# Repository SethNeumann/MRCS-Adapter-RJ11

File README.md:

# MRCS-Adapter-RJ11
## License: Creative Commons Attribution-NonCommercial-ShareAlike

MRCS - RJ modular Headset connector breakout board

RJ11/4 "mini" headset connector to 0.100 pins, for telephony applications

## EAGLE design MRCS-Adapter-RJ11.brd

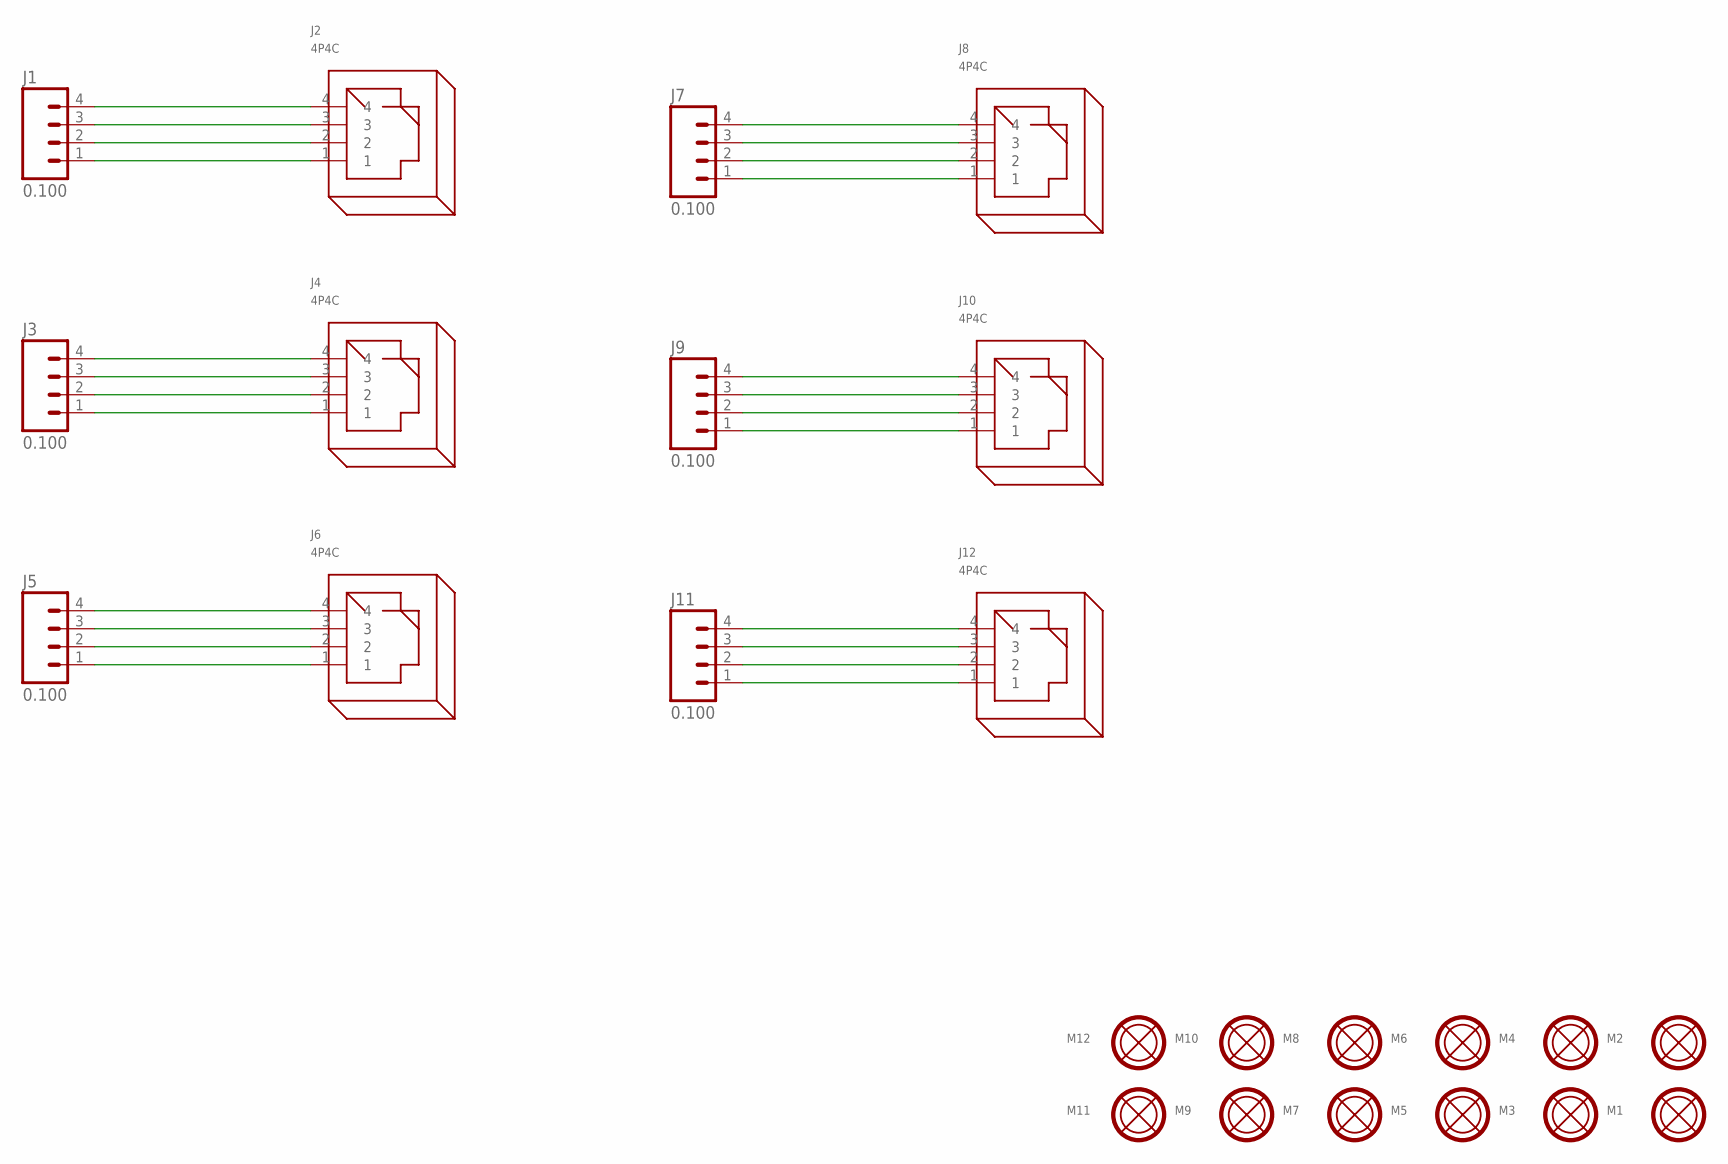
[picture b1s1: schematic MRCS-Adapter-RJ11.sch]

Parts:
J1, J3, J5, J7, J9, J11: 0.100; 1X04_LOCK
J2, J4, J6, J8, J10, J12: 4P4C; RJ11
M1, M2, M3, M4, M5, M6, M7, M8, M9, M10, M11, M12: MOUNTINGHOLE

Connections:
unnamed: J1.1, J2.1
unnamed: J1.2, J2.2
unnamed: J1.3, J2.3
unnamed: J1.4, J2.4
unnamed: J3.1, J4.1
unnamed: J3.2, J4.2
unnamed: J3.3, J4.3
unnamed: J3.4, J4.4
unnamed: J5.1, J6.1
unnamed: J5.2, J6.2
unnamed: J5.3, J6.3
unnamed: J5.4, J6.4
unnamed: J7.1, J8.1
unnamed: J7.2, J8.2
unnamed: J7.3, J8.3
unnamed: J7.4, J8.4
unnamed: J9.1, J10.1
unnamed: J9.2, J10.2
unnamed: J9.3, J10.3
unnamed: J9.4, J10.4
unnamed: J11.1, J12.1
unnamed: J11.2, J12.2
unnamed: J11.3, J12.3
unnamed: J11.4, J12.4

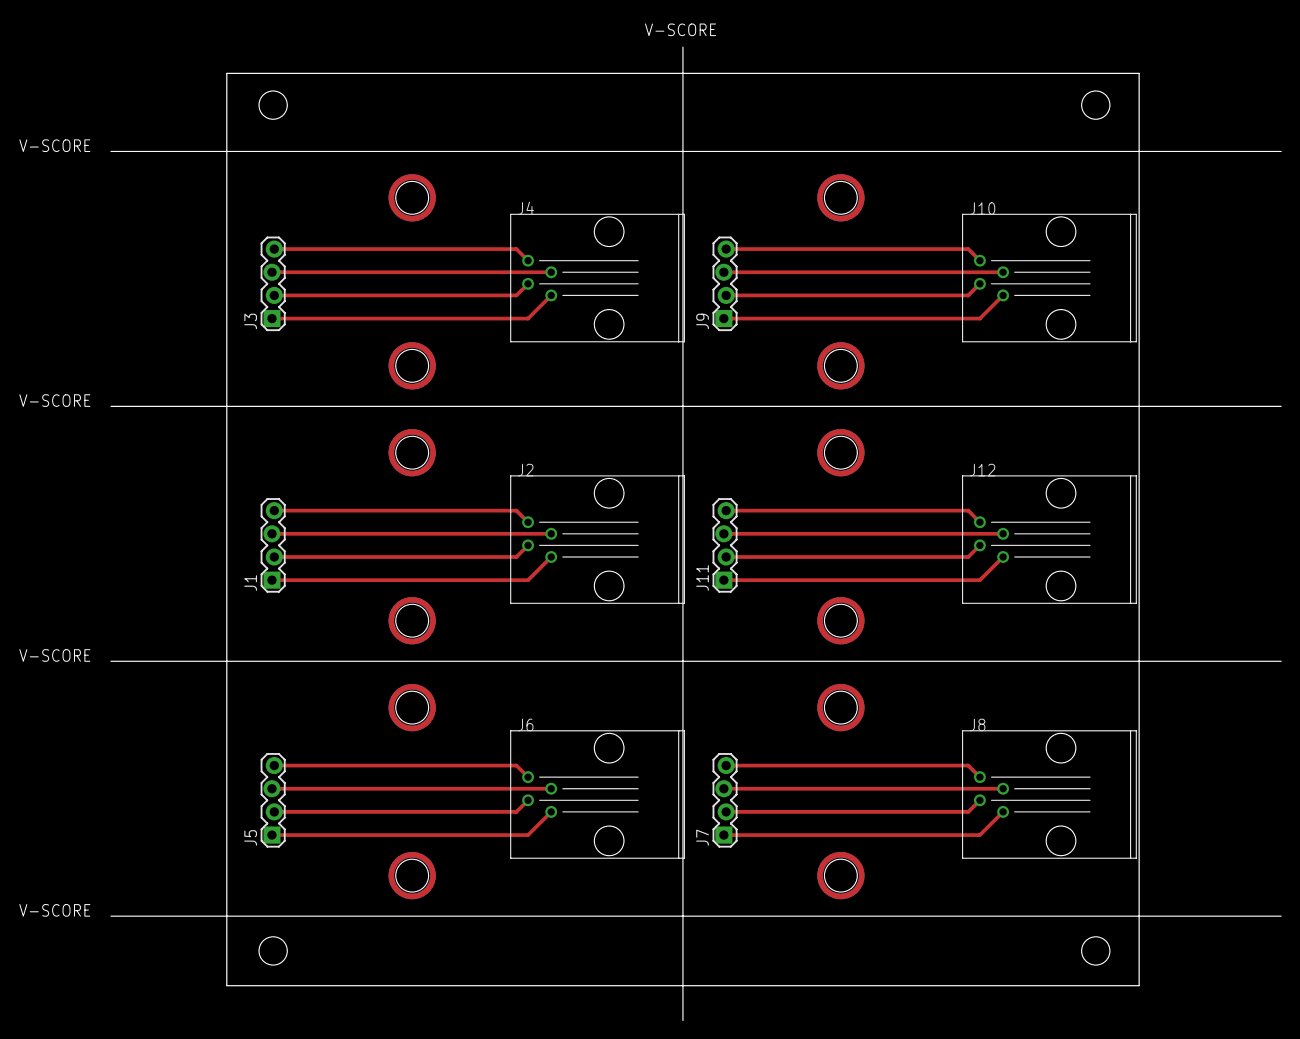
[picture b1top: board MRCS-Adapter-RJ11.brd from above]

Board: 2 copper layers, 100.0 x 100.0 mm, 31 parts (0 on the bottom side), 24 nets.

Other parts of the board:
E$1: 10x10; BOARD-10X10-3X2-PANEL
U$1, U$2, U$3, U$4, U$5, U$6: MRCS; MRCSLOGOTOP

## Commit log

2020-05-04 updated tags
2020-10-05 added missing values
2020-10-05 fixed silkscreen
